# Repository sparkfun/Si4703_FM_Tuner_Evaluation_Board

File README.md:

SparkFun FM Tuner Evaluation Board - Si4703
===========================================

[*SparkFun FM Tuner Evaluation Board - Si4703 (WRL-12938)*](https://www.sparkfun.com/products/12938)

This is an evaluation board for the Silicon Laboratories Si4703 FM tuner chip. Beyond being a simple FM radio, the Si4703 
is also capable of detecting and processing both Radio Data Service (RDS) and Radio Broadcast Data Service (RBDS) information. 

Repository Contents
-------------------
* **/Firmware** - Example code 
* **/Hardware** - Eagle design files (.brd, .sch)
* **/Libraries** - Libraries for use with the Si4703 Evaluation Board
* **/Production** - Production panel files (.brd)

Documentation
--------------
* **[Library](https://github.com/sparkfun/SparkFun_Si4703_Arduino_Library)** - Arduino and Raspberry Pi libraries for the Si4703.
* **[Hookup Guide](https://learn.sparkfun.com/tutorials/si4703-fm-radio-receiver-hookup-guide)** - Basic hookup guide for the Si4703.
* **[SparkFun Fritzing repo](https://github.com/sparkfun/Fritzing_Parts)** - Fritzing diagrams for SparkFun products.
* **[SparkFun 3D Model repo](https://github.com/sparkfun/3D_Models)** - 3D models of SparkFun products. 

License Information
-------------------
This product is _**open source**_! 

Please review the LICENSE.md file for license information. 

If you have any questions or concerns on licensing, please contact techsupport@sparkfun.com.

Distributed as-is; no warranty is given.

- Your friends at SparkFun.

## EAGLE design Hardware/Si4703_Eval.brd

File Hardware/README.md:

SparkFun Si4703 Evaluation Board Design Files
============================================

The .sch and .brd files hare are Eagle CAD schematic and PCB design files from SparkFun Electronics.
A freeware version of Eagle can be found [here](http://www.cadsoftusa.com/download-eagle/freeware/). 

License
---------
This product is open source! 
The hardware is released under [Creative Commons ShareAlike 4.0 International](https://creativecommons.org/licenses/by-sa/4.0/).

Please use, reuse, and modify these files as you see fit. Please maintain attribution to SparkFun Electronics and release anything derivative under the same license.

Distributed as-is; no warranty is given.

- Your friends at SparkFun.

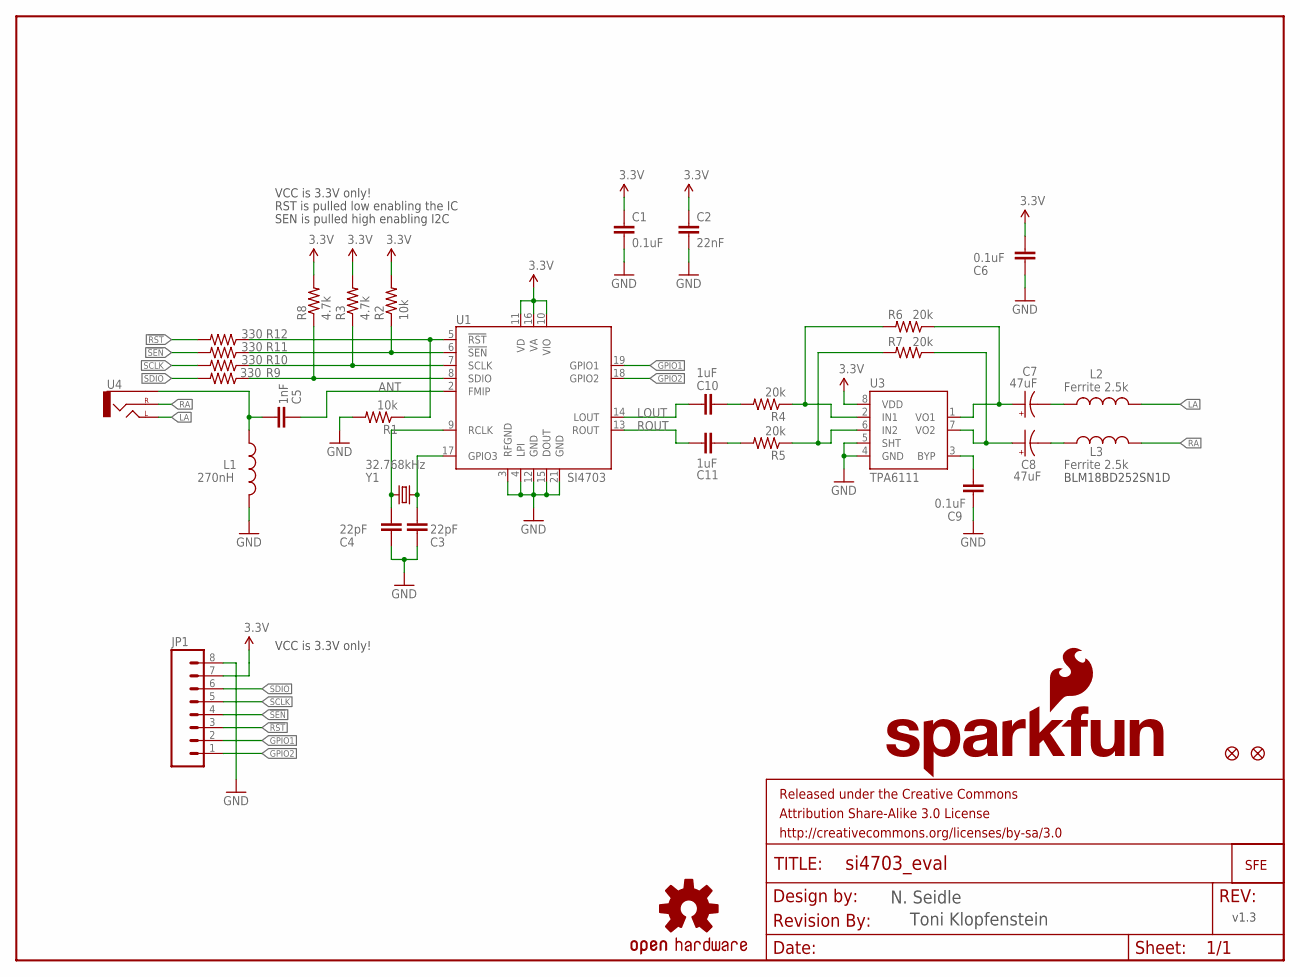
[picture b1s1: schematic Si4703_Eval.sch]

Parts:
C1, C6, C9: 0.1uF; 0603-CAP
C2: 22nF; 0603-CAP
C3, C4: 22pF; 0603-CAP
C5: 1nF; 0603-CAP
C7, C8: 47uF; EIA3528
C10, C11: 1uF; 0603-CAP
FRAME2: FRAME-LETTER; CREATIVE_COMMONS
JP1: M08; 1X08
JP3: LOGO-SFESK; SFE-LOGO-FLAME
JP4, JP5: FIDUCIAL1X2; FIDUCIAL-1X2
L1: 270nH; 0603
L2, L3: Ferrite 2.5k; 0603
LOGO1: SFE_LOGO_NAME_FLAME.1_INCH; SFE_LOGO_NAME_FLAME_.1
LOGO2: OSHW-LOGOS; OSHW-LOGO-S
R1, R2: 10k; 0603-RES
R3, R8: 4.7k; 0603
R4, R5, R6, R7: 20k; 0603-RES
R9, R10, R11, R12: 330; 0603-RES
U1: SI4703; SI470X
U3: TPA6111; SO08-TIGHT
U4: AUDIO-JACKSMD2; AUDIO-JACK-3.5MM-SMD
U$1: REVISION
Y1: 32.768kHz; CRYSTAL-32KHZ-SMD

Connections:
3.3V: C1.1, C2.1, C6.2, JP1.7, R2.2, R3.2, R8.2, U1.10 (VIO), U1.11 (VD), U1.16 (VA), U3.8 (VDD)
!RST: JP1.3, R12.2
!RST-L: R1.1, R12.1, U1.5 (!RST)
!SEN: JP1.4, R11.2
!SEN-L: R2.1, R11.1, U1.6 (!SEN)
ANT: C5.1, U1.2 (FMIP)
GND: C1.2, C2.2, C3.1, C4.1, C6.1, C9.2, JP1.8, L1.2, R1.2, U1.3 (RFGND), U1.4 (LPI), U1.12 (GND), U1.15 (DOUT), U1.21 (GND), U3.4 (GND), U3.5 (SHT)
GPIO1: JP1.2, U1.19 (GPIO1)
GPIO2: JP1.1, U1.18 (GPIO2)
LA: L2.2, U4.TIP (LEFT)
LOUT: C10.1, U1.14 (LOUT)
unnamed: C4.2, U1.9 (RCLK), Y1.X2 (2)
unnamed: C3.2, U1.17 (GPIO3), Y1.X1 (1)
unnamed: C5.2, L1.1, U4.SLEEVE
unnamed: C7.C (-), L2.1
unnamed: C7.A (+), R6.1, U3.1 (VO1)
unnamed: C8.A (+), R7.1, U3.7 (VO2)
unnamed: C8.C (-), L3.1
unnamed: C9.1, U3.3 (BYP)
unnamed: R4.1, R6.2, U3.2 (IN1)
unnamed: R5.1, R7.2, U3.6 (IN2)
unnamed: C10.2, R4.2
unnamed: C11.2, R5.2
RA: L3.2, U4.RING (RIGHT)
ROUT: C11.1, U1.13 (ROUT)
SCLK: JP1.5, R10.2
SCLK-L: R3.1, R10.1, U1.7 (SCLK)
SDIO: JP1.6, R9.2
SDIO-L: R8.1, R9.1, U1.8 (SDIO)

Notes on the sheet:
VCC is 3.3V only!
N. Seidle
BLM18BD252SN1D
SEN is pulled high enabling I2C
RST is pulled low enabling the IC
v1.3
Toni Klopfenstein

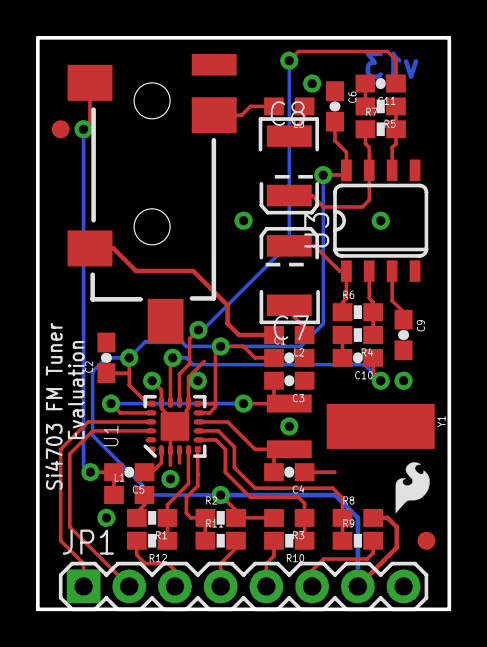
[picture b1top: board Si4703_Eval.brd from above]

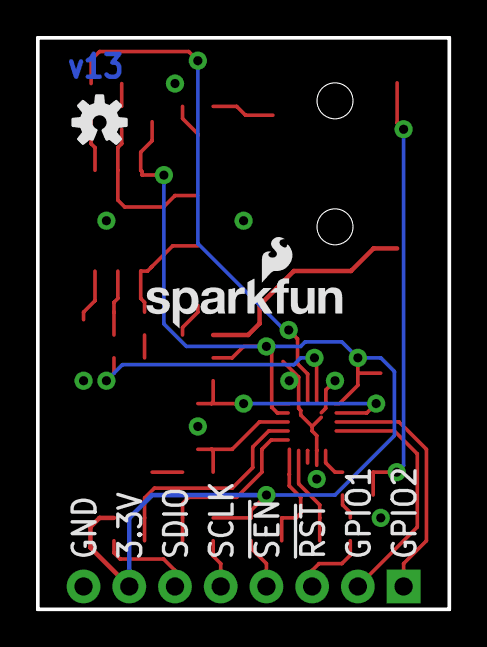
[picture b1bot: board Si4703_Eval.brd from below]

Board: 2 copper layers, 22.9 x 31.8 mm, 38 parts (2 on the bottom side), 29 nets.

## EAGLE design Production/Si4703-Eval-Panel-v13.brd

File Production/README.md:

SparkFun Si4703 Evaluation Board Production Files
==================================================

These are the production files SparkFun uses for printing PCBs.

License Information
-------------------
This product is open source! 

The hardware is released under [Creative Commons ShareAlike 4.0 International](https://creativecommons.org/licenses/by-sa/4.0/).

Please use, reuse, and modify these files as you see fit. Please maintain attribution to SparkFun Electronics and release anything derivative under the same license.

Distributed as-is; no warranty is given.

- Your friends at SparkFun.

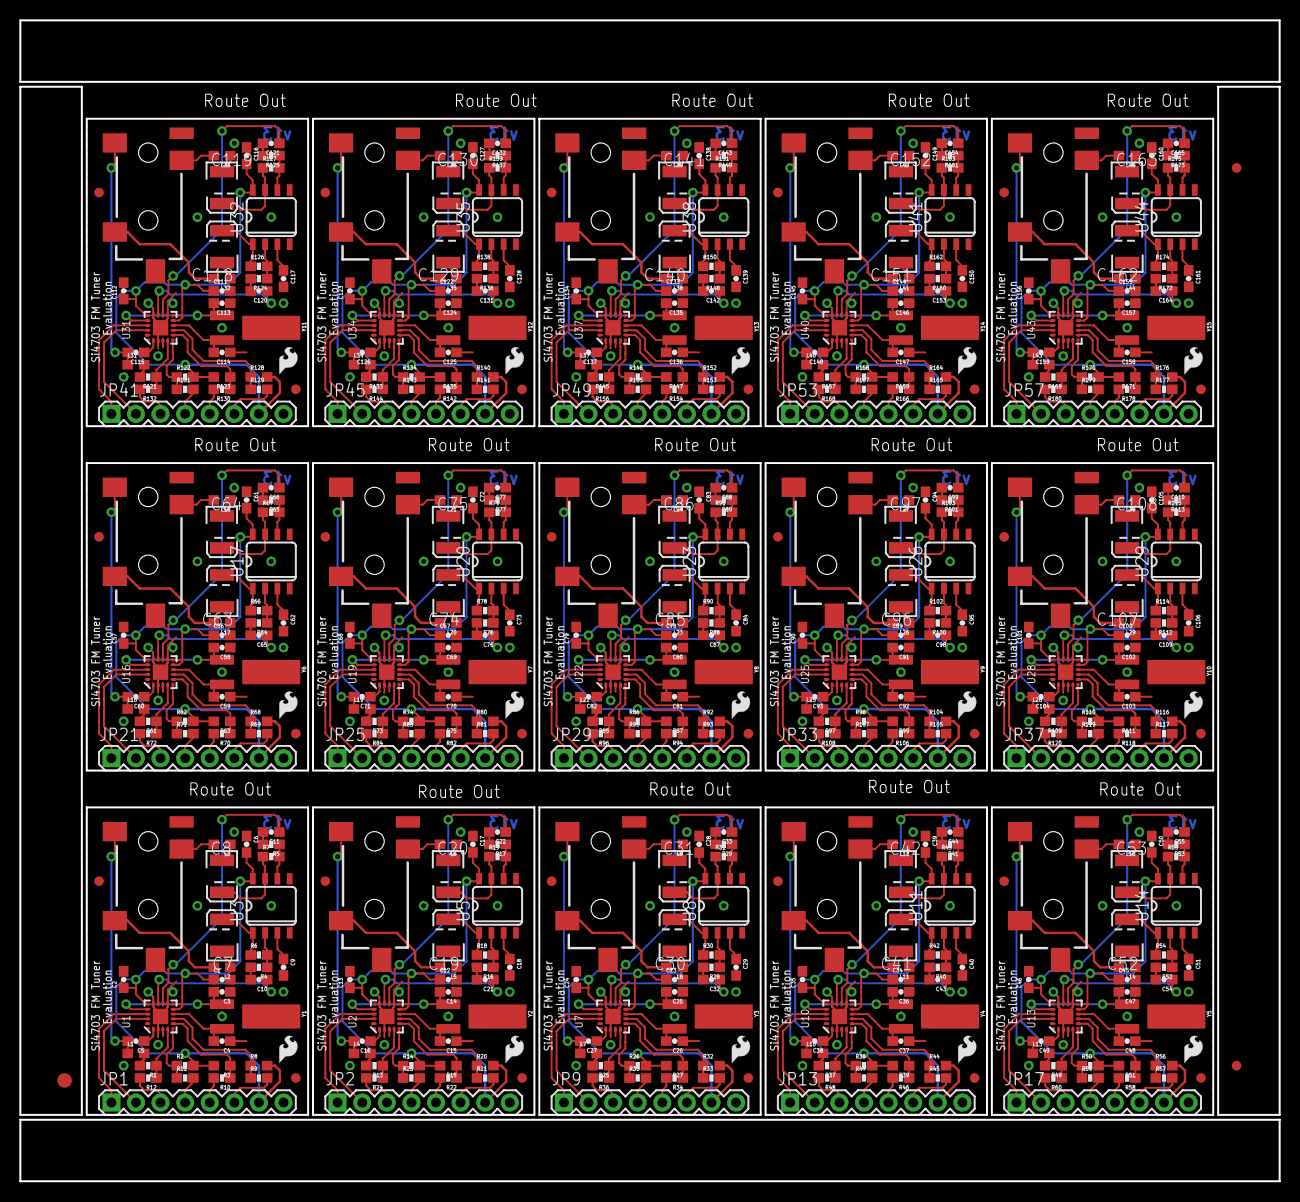
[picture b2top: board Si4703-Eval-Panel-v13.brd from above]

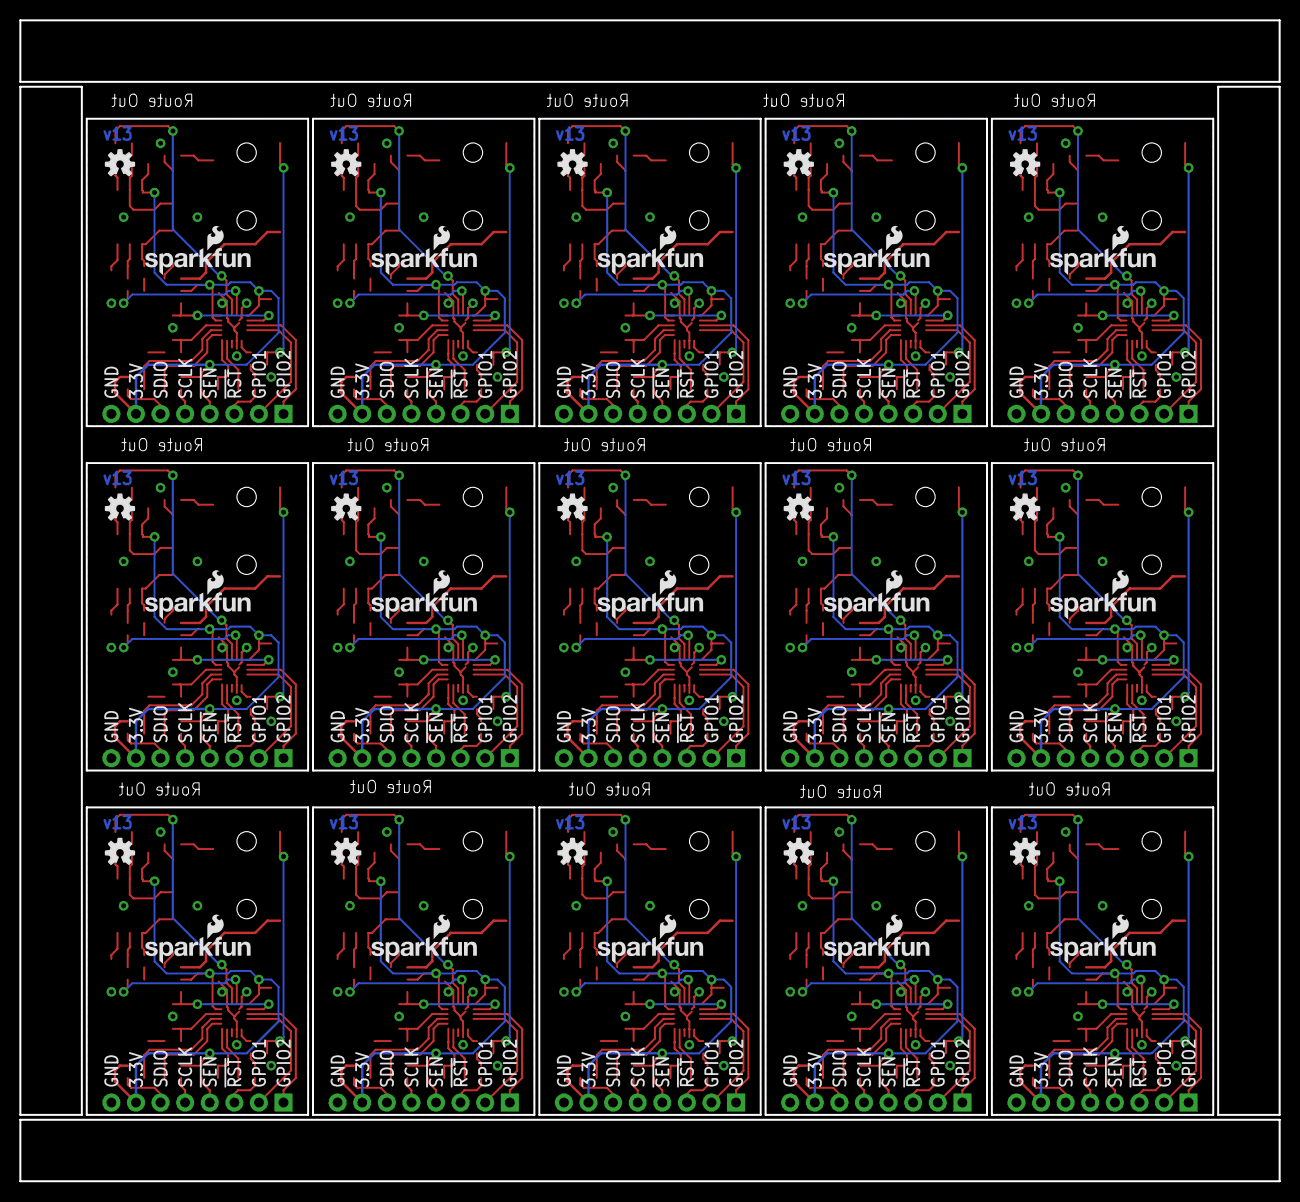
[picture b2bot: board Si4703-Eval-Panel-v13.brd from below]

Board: 2 copper layers, 130.0 x 119.9 mm, 543 parts (30 on the bottom side), 435 nets.

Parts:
C1, C6, C9, C12, C17, C18, C23, C28, C29, C34, C39, C40, C45, C50, C51, C56, C61, C62, C67, C72, C73, C78, C83, C84, C89, C94, C95, C100, C105, C106, C111, C116, C117, C122, C127, C128, C133, C138, C139, C144, C149, C150, C155, C160, C161: 0.1uF; 0603-CAP
C2, C13, C24, C35, C46, C57, C68, C79, C90, C101, C112, C123, C134, C145, C156: 22nF; 0603-CAP
C3, C4, C14, C15, C25, C26, C36, C37, C47, C48, C58, C59, C69, C70, C80, C81, C91, C92, C102, C103, C113, C114, C124, C125, C135, C136, C146, C147, C157, C158: 22pF; 0603-CAP
C5, C16, C27, C38, C49, C60, C71, C82, C93, C104, C115, C126, C137, C148, C159: 1nF; 0603-CAP
C7, C8, C19, C20, C30, C31, C41, C42, C52, C53, C63, C64, C74, C75, C85, C86, C96, C97, C107, C108, C118, C119, C129, C130, C140, C141, C151, C152, C162, C163: 47uF; EIA3528
C10, C11, C21, C22, C32, C33, C43, C44, C54, C55, C65, C66, C76, C77, C87, C88, C98, C99, C109, C110, C120, C121, C131, C132, C142, C143, C153, C154, C164, C165: 1uF; 0603-CAP
E$1: FIDUCIAL-1.5X3
E$4, E$5: FIDUCIAL-1X2
JP1, JP2, JP9, JP13, JP17, JP21, JP25, JP29, JP33, JP37, JP41, JP45, JP49, JP53, JP57: 1X08
JP3, JP6, JP10, JP14, JP18, JP22, JP26, JP30, JP34, JP38, JP42, JP46, JP50, JP54, JP58: LOGO-SFESK; SFE-LOGO-FLAME
JP4, JP5, JP7, JP8, JP11, JP12, JP15, JP16, JP19, JP20, JP23, JP24, JP27, JP28, JP31, JP32, JP35, JP36, JP39, JP40, JP43, JP44, JP47, JP48, JP51, JP52, JP55, JP56, JP59, JP60: FIDUCIAL1X2; FIDUCIAL-1X2
L1, L4, L7, L10, L13, L16, L19, L22, L25, L28, L31, L34, L37, L40, L43: 270nH; 0603
L2, L3, L5, L6, L8, L9, L11, L12, L14, L15, L17, L18, L20, L21, L23, L24, L26, L27, L29, L30, L32, L33, L35, L36, L38, L39, L41, L42, L44, L45: Ferrite 2.5k; 0603
LOGO1, LOGO3, LOGO5, LOGO7, LOGO9, LOGO11, LOGO13, LOGO15, LOGO17, LOGO19, LOGO21, LOGO23, LOGO25, LOGO27, LOGO29: SFE_LOGO_NAME_FLAME.1_INCH; SFE_LOGO_NAME_FLAME_.1
LOGO2, LOGO4, LOGO6, LOGO8, LOGO10, LOGO12, LOGO14, LOGO16, LOGO18, LOGO20, LOGO22, LOGO24, LOGO26, LOGO28, LOGO30: OSHW-LOGOS; OSHW-LOGO-S
R1, R2, R13, R14, R25, R26, R37, R38, R49, R50, R61, R62, R73, R74, R85, R86, R97, R98, R109, R110, R121, R122, R133, R134, R145, R146, R157, R158, R169, R170: 10k; 0603-RES
R3, R8, R15, R20, R27, R32, R39, R44, R51, R56, R63, R68, R75, R80, R87, R92, R99, R104, R111, R116, R123, R128, R135, R140, R147, R152, R159, R164, R171, R176: 4.7k; 0603
R4, R5, R6, R7, R16, R17, R18, R19, R28, R29, R30, R31, R40, R41, R42, R43, R52, R53, R54, R55, R64, R65, R66, R67, R76, R77, R78, R79, R88, R89, R90, R91, R100, R101, R102, R103, R112, R113, R114, R115, R124, R125, R126, R127, R136, R137, R138, R139, R148, R149, R150, R151, R160, R161, R162, R163, R172, R173, R174, R175: 20k; 0603-RES
R9, R10, R11, R12, R21, R22, R23, R24, R33, R34, R35, R36, R45, R46, R47, R48, R57, R58, R59, R60, R69, R70, R71, R72, R81, R82, R83, R84, R93, R94, R95, R96, R105, R106, R107, R108, R117, R118, R119, R120, R129, R130, R131, R132, R141, R142, R143, R144, R153, R154, R155, R156, R165, R166, R167, R168, R177, R178, R179, R180: 330; 0603-RES
U1, U2, U7, U10, U13, U16, U19, U22, U25, U28, U31, U34, U37, U40, U43: SI4703; SI470X
U3, U5, U8, U11, U14, U17, U20, U23, U26, U29, U32, U35, U38, U41, U44: TPA6111; SO08-TIGHT
U4, U6, U9, U12, U15, U18, U21, U24, U27, U30, U33, U36, U39, U42, U45: AUDIO-JACK-3.5MM-SMD
Y1, Y2, Y3, Y4, Y5, Y6, Y7, Y8, Y9, Y10, Y11, Y12, Y13, Y14, Y15: 32.768kHz; CRYSTAL-32KHZ-SMD

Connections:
3.3V: C1.1, C2.1, C6.2, JP1.7, R2.2, R3.2, R8.2, U1.10, U1.11, U1.16, U3.8
3.3V1: C12.1, C13.1, C17.2, JP2.7, R14.2, R15.2, R20.2, U2.10, U2.11, U2.16, U5.8
3.3V2: C23.1, C24.1, C28.2, JP9.7, R26.2, R27.2, R32.2, U7.10, U7.11, U7.16, U8.8
3.3V3: C34.1, C35.1, C39.2, JP13.7, R38.2, R39.2, R44.2, U10.10, U10.11, U10.16, U11.8
3.3V4: C45.1, C46.1, C50.2, JP17.7, R50.2, R51.2, R56.2, U13.10, U13.11, U13.16, U14.8
3.3V5: C56.1, C57.1, C61.2, JP21.7, R62.2, R63.2, R68.2, U16.10, U16.11, U16.16, U17.8
3.3V6: C67.1, C68.1, C72.2, JP25.7, R74.2, R75.2, R80.2, U19.10, U19.11, U19.16, U20.8
3.3V7: C78.1, C79.1, C83.2, JP29.7, R86.2, R87.2, R92.2, U22.10, U22.11, U22.16, U23.8
3.3V8: C89.1, C90.1, C94.2, JP33.7, R98.2, R99.2, R104.2, U25.10, U25.11, U25.16, U26.8
3.3V9: C100.1, C101.1, C105.2, JP37.7, R110.2, R111.2, R116.2, U28.10, U28.11, U28.16, U29.8
3.3V10: C111.1, C112.1, C116.2, JP41.7, R122.2, R123.2, R128.2, U31.10, U31.11, U31.16, U32.8
3.3V11: C122.1, C123.1, C127.2, JP45.7, R134.2, R135.2, R140.2, U34.10, U34.11, U34.16, U35.8
3.3V12: C133.1, C134.1, C138.2, JP49.7, R146.2, R147.2, R152.2, U37.10, U37.11, U37.16, U38.8
3.3V13: C144.1, C145.1, C149.2, JP53.7, R158.2, R159.2, R164.2, U40.10, U40.11, U40.16, U41.8
3.3V14: C155.1, C156.1, C160.2, JP57.7, R170.2, R171.2, R176.2, U43.10, U43.11, U43.16, U44.8
!RST: JP1.3, R12.2
!RST1: JP2.3, R24.2
!RST2: JP9.3, R36.2
!RST3: JP13.3, R48.2
!RST4: JP17.3, R60.2
!RST5: JP21.3, R72.2
!RST6: JP25.3, R84.2
!RST7: JP29.3, R96.2
!RST8: JP33.3, R108.2
!RST9: JP37.3, R120.2
!RST10: JP41.3, R132.2
!RST11: JP45.3, R144.2
!RST12: JP49.3, R156.2
!RST13: JP53.3, R168.2
!RST14: JP57.3, R180.2
!RST-L: R1.1, R12.1, U1.5
!RST-L1: R13.1, R24.1, U2.5
!RST-L2: R25.1, R36.1, U7.5
!RST-L3: R37.1, R48.1, U10.5
!RST-L4: R49.1, R60.1, U13.5
!RST-L5: R61.1, R72.1, U16.5
!RST-L6: R73.1, R84.1, U19.5
!RST-L7: R85.1, R96.1, U22.5
!RST-L8: R97.1, R108.1, U25.5
!RST-L9: R109.1, R120.1, U28.5
!RST-L10: R121.1, R132.1, U31.5
!RST-L11: R133.1, R144.1, U34.5
!RST-L12: R145.1, R156.1, U37.5
!RST-L13: R157.1, R168.1, U40.5
!RST-L14: R169.1, R180.1, U43.5
!SEN: JP1.4, R11.2
!SEN1: JP2.4, R23.2
!SEN2: JP9.4, R35.2
!SEN3: JP13.4, R47.2
!SEN4: JP17.4, R59.2
!SEN5: JP21.4, R71.2
!SEN6: JP25.4, R83.2
!SEN7: JP29.4, R95.2
!SEN8: JP33.4, R107.2
!SEN9: JP37.4, R119.2
!SEN10: JP41.4, R131.2
!SEN11: JP45.4, R143.2
!SEN12: JP49.4, R155.2
!SEN13: JP53.4, R167.2
!SEN14: JP57.4, R179.2
!SEN-L: R2.1, R11.1, U1.6
!SEN-L1: R14.1, R23.1, U2.6
!SEN-L2: R26.1, R35.1, U7.6
!SEN-L3: R38.1, R47.1, U10.6
!SEN-L4: R50.1, R59.1, U13.6
!SEN-L5: R62.1, R71.1, U16.6
!SEN-L6: R74.1, R83.1, U19.6
!SEN-L7: R86.1, R95.1, U22.6
!SEN-L8: R98.1, R107.1, U25.6
!SEN-L9: R110.1, R119.1, U28.6
!SEN-L10: R122.1, R131.1, U31.6
!SEN-L11: R134.1, R143.1, U34.6
!SEN-L12: R146.1, R155.1, U37.6
!SEN-L13: R158.1, R167.1, U40.6
!SEN-L14: R170.1, R179.1, U43.6
ANT: C5.1, U1.2
ANT1: C16.1, U2.2
ANT2: C27.1, U7.2
ANT3: C38.1, U10.2
ANT4: C49.1, U13.2
ANT5: C60.1, U16.2
ANT6: C71.1, U19.2
ANT7: C82.1, U22.2
ANT8: C93.1, U25.2
ANT9: C104.1, U28.2
ANT10: C115.1, U31.2
ANT11: C126.1, U34.2
ANT12: C137.1, U37.2
ANT13: C148.1, U40.2
ANT14: C159.1, U43.2
GND: C1.2, C2.2, C3.1, C4.1, C6.1, C9.2, JP1.8, L1.2, R1.2, U1.3, U1.4, U1.12, U1.15, U1.21, U3.4, U3.5
GND1: C12.2, C13.2, C14.1, C15.1, C17.1, C18.2, JP2.8, L4.2, R13.2, U2.3, U2.4, U2.12, U2.15, U2.21, U5.4, U5.5
GND2: C23.2, C24.2, C25.1, C26.1, C28.1, C29.2, JP9.8, L7.2, R25.2, U7.3, U7.4, U7.12, U7.15, U7.21, U8.4, U8.5
GND3: C34.2, C35.2, C36.1, C37.1, C39.1, C40.2, JP13.8, L10.2, R37.2, U10.3, U10.4, U10.12, U10.15, U10.21, U11.4, U11.5
GND4: C45.2, C46.2, C47.1, C48.1, C50.1, C51.2, JP17.8, L13.2, R49.2, U13.3, U13.4, U13.12, U13.15, U13.21, U14.4, U14.5
GND5: C56.2, C57.2, C58.1, C59.1, C61.1, C62.2, JP21.8, L16.2, R61.2, U16.3, U16.4, U16.12, U16.15, U16.21, U17.4, U17.5
GND6: C67.2, C68.2, C69.1, C70.1, C72.1, C73.2, JP25.8, L19.2, R73.2, U19.3, U19.4, U19.12, U19.15, U19.21, U20.4, U20.5
GND7: C78.2, C79.2, C80.1, C81.1, C83.1, C84.2, JP29.8, L22.2, R85.2, U22.3, U22.4, U22.12, U22.15, U22.21, U23.4, U23.5
GND8: C89.2, C90.2, C91.1, C92.1, C94.1, C95.2, JP33.8, L25.2, R97.2, U25.3, U25.4, U25.12, U25.15, U25.21, U26.4, U26.5
GND9: C100.2, C101.2, C102.1, C103.1, C105.1, C106.2, JP37.8, L28.2, R109.2, U28.3, U28.4, U28.12, U28.15, U28.21, U29.4, U29.5
GND10: C111.2, C112.2, C113.1, C114.1, C116.1, C117.2, JP41.8, L31.2, R121.2, U31.3, U31.4, U31.12, U31.15, U31.21, U32.4, U32.5
GND11: C122.2, C123.2, C124.1, C125.1, C127.1, C128.2, JP45.8, L34.2, R133.2, U34.3, U34.4, U34.12, U34.15, U34.21, U35.4, U35.5
GND12: C133.2, C134.2, C135.1, C136.1, C138.1, C139.2, JP49.8, L37.2, R145.2, U37.3, U37.4, U37.12, U37.15, U37.21, U38.4, U38.5
GND13: C144.2, C145.2, C146.1, C147.1, C149.1, C150.2, JP53.8, L40.2, R157.2, U40.3, U40.4, U40.12, U40.15, U40.21, U41.4, U41.5
GND14: C155.2, C156.2, C157.1, C158.1, C160.1, C161.2, JP57.8, L43.2, R169.2, U43.3, U43.4, U43.12, U43.15, U43.21, U44.4, U44.5
GPIO1: JP1.2, U1.19
GPIO2: JP1.1, U1.18
GPIO3: JP2.2, U2.19
GPIO4: JP2.1, U2.18
GPIO5: JP9.2, U7.19
GPIO6: JP9.1, U7.18
GPIO7: JP13.2, U10.19
GPIO8: JP13.1, U10.18
GPIO9: JP17.2, U13.19
GPIO10: JP17.1, U13.18
GPIO11: JP21.2, U16.19
GPIO12: JP21.1, U16.18
GPIO13: JP25.2, U19.19
GPIO14: JP25.1, U19.18
GPIO15: JP29.2, U22.19
GPIO16: JP29.1, U22.18
GPIO17: JP33.2, U25.19
GPIO18: JP33.1, U25.18
GPIO19: JP37.2, U28.19
GPIO20: JP37.1, U28.18
GPIO21: JP41.2, U31.19
GPIO22: JP41.1, U31.18
GPIO23: JP45.2, U34.19
GPIO24: JP45.1, U34.18
GPIO25: JP49.2, U37.19
GPIO26: JP49.1, U37.18
GPIO27: JP53.2, U40.19
GPIO28: JP53.1, U40.18
GPIO29: JP57.2, U43.19
GPIO30: JP57.1, U43.18
LA: L2.2, U4.TIP
LA1: L5.2, U6.TIP
LA2: L8.2, U9.TIP
LA3: L11.2, U12.TIP
LA4: L14.2, U15.TIP
LA5: L17.2, U18.TIP
LA6: L20.2, U21.TIP
LA7: L23.2, U24.TIP
LA8: L26.2, U27.TIP
LA9: L29.2, U30.TIP
LA10: L32.2, U33.TIP
LA11: L35.2, U36.TIP
LA12: L38.2, U39.TIP
LA13: L41.2, U42.TIP
LA14: L44.2, U45.TIP
LOUT: C10.1, U1.14
LOUT1: C21.1, U2.14
LOUT2: C32.1, U7.14
LOUT3: C43.1, U10.14
LOUT4: C54.1, U13.14
LOUT5: C65.1, U16.14
LOUT6: C76.1, U19.14
LOUT7: C87.1, U22.14
LOUT8: C98.1, U25.14
LOUT9: C109.1, U28.14
LOUT10: C120.1, U31.14
LOUT11: C131.1, U34.14
LOUT12: C142.1, U37.14
LOUT13: C153.1, U40.14
LOUT14: C164.1, U43.14
unnamed: C4.2, U1.9, Y1.X2
unnamed: C3.2, U1.17, Y1.X1
unnamed: C5.2, L1.1, U4.SLEEVE
unnamed: C7.C, L2.1
unnamed: C7.A, R6.1, U3.1
unnamed: C8.A, R7.1, U3.7
unnamed: C8.C, L3.1
unnamed: C9.1, U3.3
unnamed: C15.2, U2.9, Y2.X2
unnamed: C14.2, U2.17, Y2.X1
unnamed: R4.1, R6.2, U3.2
unnamed: R5.1, R7.2, U3.6
unnamed: C10.2, R4.2
unnamed: C11.2, R5.2
unnamed: C16.2, L4.1, U6.SLEEVE
unnamed: C19.A, R18.1, U5.1
unnamed: C20.A, R19.1, U5.7
unnamed: C18.1, U5.3
unnamed: R16.1, R18.2, U5.2
unnamed: R17.1, R19.2, U5.6
unnamed: C21.2, R16.2
unnamed: C22.2, R17.2
unnamed: C19.C, L5.1
unnamed: C20.C, L6.1
unnamed: C26.2, U7.9, Y3.X2
unnamed: C25.2, U7.17, Y3.X1
unnamed: C27.2, L7.1, U9.SLEEVE
unnamed: C30.A, R30.1, U8.1
unnamed: C31.A, R31.1, U8.7
unnamed: C29.1, U8.3
unnamed: R28.1, R30.2, U8.2
unnamed: R29.1, R31.2, U8.6
unnamed: C32.2, R28.2
unnamed: C33.2, R29.2
unnamed: C30.C, L8.1
unnamed: C31.C, L9.1
unnamed: C37.2, U10.9, Y4.X2
unnamed: C36.2, U10.17, Y4.X1
unnamed: C38.2, L10.1, U12.SLEEVE
unnamed: C41.A, R42.1, U11.1
unnamed: C42.A, R43.1, U11.7
unnamed: C40.1, U11.3
unnamed: R40.1, R42.2, U11.2
unnamed: R41.1, R43.2, U11.6
unnamed: C43.2, R40.2
unnamed: C44.2, R41.2
unnamed: C41.C, L11.1
unnamed: C42.C, L12.1
unnamed: C48.2, U13.9, Y5.X2
unnamed: C47.2, U13.17, Y5.X1
unnamed: C49.2, L13.1, U15.SLEEVE
unnamed: C52.A, R54.1, U14.1
unnamed: C53.A, R55.1, U14.7
unnamed: C51.1, U14.3
unnamed: R52.1, R54.2, U14.2
unnamed: R53.1, R55.2, U14.6
unnamed: C54.2, R52.2
unnamed: C55.2, R53.2
unnamed: C52.C, L14.1
unnamed: C53.C, L15.1
unnamed: C59.2, U16.9, Y6.X2
unnamed: C58.2, U16.17, Y6.X1
unnamed: C60.2, L16.1, U18.SLEEVE
unnamed: C63.A, R66.1, U17.1
unnamed: C64.A, R67.1, U17.7
unnamed: C62.1, U17.3
unnamed: R64.1, R66.2, U17.2
unnamed: R65.1, R67.2, U17.6
unnamed: C65.2, R64.2
unnamed: C66.2, R65.2
unnamed: C63.C, L17.1
unnamed: C64.C, L18.1
unnamed: C70.2, U19.9, Y7.X2
unnamed: C69.2, U19.17, Y7.X1
unnamed: C71.2, L19.1, U21.SLEEVE
unnamed: C74.A, R78.1, U20.1
unnamed: C75.A, R79.1, U20.7
unnamed: C73.1, U20.3
unnamed: R76.1, R78.2, U20.2
unnamed: R77.1, R79.2, U20.6
unnamed: C76.2, R76.2
unnamed: C77.2, R77.2
unnamed: C74.C, L20.1
unnamed: C75.C, L21.1
unnamed: C81.2, U22.9, Y8.X2
unnamed: C80.2, U22.17, Y8.X1
unnamed: C82.2, L22.1, U24.SLEEVE
unnamed: C85.A, R90.1, U23.1
unnamed: C86.A, R91.1, U23.7
unnamed: C84.1, U23.3
unnamed: R88.1, R90.2, U23.2
unnamed: R89.1, R91.2, U23.6
unnamed: C87.2, R88.2
unnamed: C88.2, R89.2
unnamed: C85.C, L23.1
unnamed: C86.C, L24.1
unnamed: C92.2, U25.9, Y9.X2
unnamed: C91.2, U25.17, Y9.X1
unnamed: C93.2, L25.1, U27.SLEEVE
unnamed: C96.A, R102.1, U26.1
unnamed: C97.A, R103.1, U26.7
unnamed: C95.1, U26.3
unnamed: R100.1, R102.2, U26.2
unnamed: R101.1, R103.2, U26.6
unnamed: C98.2, R100.2
unnamed: C99.2, R101.2
unnamed: C96.C, L26.1
unnamed: C97.C, L27.1
unnamed: C103.2, U28.9, Y10.X2
unnamed: C102.2, U28.17, Y10.X1
unnamed: C104.2, L28.1, U30.SLEEVE
unnamed: C107.A, R114.1, U29.1
unnamed: C108.A, R115.1, U29.7
unnamed: C106.1, U29.3
unnamed: R112.1, R114.2, U29.2
unnamed: R113.1, R115.2, U29.6
unnamed: C109.2, R112.2
unnamed: C110.2, R113.2
unnamed: C107.C, L29.1
unnamed: C108.C, L30.1
unnamed: C114.2, U31.9, Y11.X2
unnamed: C113.2, U31.17, Y11.X1
unnamed: C115.2, L31.1, U33.SLEEVE
unnamed: C118.A, R126.1, U32.1
unnamed: C119.A, R127.1, U32.7
unnamed: C117.1, U32.3
unnamed: R124.1, R126.2, U32.2
unnamed: R125.1, R127.2, U32.6
unnamed: C120.2, R124.2
unnamed: C121.2, R125.2
unnamed: C118.C, L32.1
unnamed: C119.C, L33.1
unnamed: C125.2, U34.9, Y12.X2
unnamed: C124.2, U34.17, Y12.X1
unnamed: C126.2, L34.1, U36.SLEEVE
unnamed: C129.A, R138.1, U35.1
unnamed: C130.A, R139.1, U35.7
unnamed: C128.1, U35.3
unnamed: R136.1, R138.2, U35.2
unnamed: R137.1, R139.2, U35.6
unnamed: C131.2, R136.2
unnamed: C132.2, R137.2
unnamed: C129.C, L35.1
unnamed: C130.C, L36.1
unnamed: C136.2, U37.9, Y13.X2
unnamed: C135.2, U37.17, Y13.X1
unnamed: C137.2, L37.1, U39.SLEEVE
unnamed: C140.A, R150.1, U38.1
unnamed: C141.A, R151.1, U38.7
unnamed: C139.1, U38.3
unnamed: R148.1, R150.2, U38.2
unnamed: R149.1, R151.2, U38.6
unnamed: C142.2, R148.2
unnamed: C143.2, R149.2
unnamed: C140.C, L38.1
unnamed: C141.C, L39.1
unnamed: C147.2, U40.9, Y14.X2
unnamed: C146.2, U40.17, Y14.X1
unnamed: C148.2, L40.1, U42.SLEEVE
unnamed: C151.A, R162.1, U41.1
unnamed: C152.A, R163.1, U41.7
unnamed: C150.1, U41.3
unnamed: R160.1, R162.2, U41.2
unnamed: R161.1, R163.2, U41.6
unnamed: C153.2, R160.2
unnamed: C154.2, R161.2
unnamed: C151.C, L41.1
unnamed: C152.C, L42.1
unnamed: C158.2, U43.9, Y15.X2
unnamed: C157.2, U43.17, Y15.X1
unnamed: C159.2, L43.1, U45.SLEEVE
unnamed: C162.A, R174.1, U44.1
unnamed: C163.A, R175.1, U44.7
unnamed: C161.1, U44.3
unnamed: R172.1, R174.2, U44.2
unnamed: R173.1, R175.2, U44.6
unnamed: C164.2, R172.2
unnamed: C165.2, R173.2
unnamed: C162.C, L44.1
unnamed: C163.C, L45.1
RA: L3.2, U4.RING
RA1: L6.2, U6.RING
RA2: L9.2, U9.RING
RA3: L12.2, U12.RING
RA4: L15.2, U15.RING
RA5: L18.2, U18.RING
RA6: L21.2, U21.RING
RA7: L24.2, U24.RING
RA8: L27.2, U27.RING
RA9: L30.2, U30.RING
RA10: L33.2, U33.RING
RA11: L36.2, U36.RING
RA12: L39.2, U39.RING
RA13: L42.2, U42.RING
RA14: L45.2, U45.RING
ROUT: C11.1, U1.13
ROUT1: C22.1, U2.13
ROUT2: C33.1, U7.13
ROUT3: C44.1, U10.13
ROUT4: C55.1, U13.13
ROUT5: C66.1, U16.13
ROUT6: C77.1, U19.13
ROUT7: C88.1, U22.13
ROUT8: C99.1, U25.13
ROUT9: C110.1, U28.13
ROUT10: C121.1, U31.13
ROUT11: C132.1, U34.13
ROUT12: C143.1, U37.13
ROUT13: C154.1, U40.13
ROUT14: C165.1, U43.13
SCLK: JP1.5, R10.2
SCLK1: JP2.5, R22.2
SCLK2: JP9.5, R34.2
SCLK3: JP13.5, R46.2
SCLK4: JP17.5, R58.2
SCLK5: JP21.5, R70.2
SCLK6: JP25.5, R82.2
SCLK7: JP29.5, R94.2
SCLK8: JP33.5, R106.2
SCLK9: JP37.5, R118.2
SCLK10: JP41.5, R130.2
SCLK11: JP45.5, R142.2
SCLK12: JP49.5, R154.2
SCLK13: JP53.5, R166.2
SCLK14: JP57.5, R178.2
SCLK-L: R3.1, R10.1, U1.7
SCLK-L1: R15.1, R22.1, U2.7
SCLK-L2: R27.1, R34.1, U7.7
SCLK-L3: R39.1, R46.1, U10.7
SCLK-L4: R51.1, R58.1, U13.7
SCLK-L5: R63.1, R70.1, U16.7
SCLK-L6: R75.1, R82.1, U19.7
SCLK-L7: R87.1, R94.1, U22.7
SCLK-L8: R99.1, R106.1, U25.7
SCLK-L9: R111.1, R118.1, U28.7
SCLK-L10: R123.1, R130.1, U31.7
SCLK-L11: R135.1, R142.1, U34.7
SCLK-L12: R147.1, R154.1, U37.7
SCLK-L13: R159.1, R166.1, U40.7
SCLK-L14: R171.1, R178.1, U43.7
SDIO: JP1.6, R9.2
SDIO1: JP2.6, R21.2
SDIO2: JP9.6, R33.2
SDIO3: JP13.6, R45.2
SDIO4: JP17.6, R57.2
SDIO5: JP21.6, R69.2
SDIO6: JP25.6, R81.2
SDIO7: JP29.6, R93.2
SDIO8: JP33.6, R105.2
SDIO9: JP37.6, R117.2
SDIO10: JP41.6, R129.2
SDIO11: JP45.6, R141.2
SDIO12: JP49.6, R153.2
SDIO13: JP53.6, R165.2
SDIO14: JP57.6, R177.2
SDIO-L: R8.1, R9.1, U1.8
SDIO-L1: R20.1, R21.1, U2.8
SDIO-L2: R32.1, R33.1, U7.8
SDIO-L3: R44.1, R45.1, U10.8
SDIO-L4: R56.1, R57.1, U13.8
SDIO-L5: R68.1, R69.1, U16.8
SDIO-L6: R80.1, R81.1, U19.8
SDIO-L7: R92.1, R93.1, U22.8
SDIO-L8: R104.1, R105.1, U25.8
SDIO-L9: R116.1, R117.1, U28.8
SDIO-L10: R128.1, R129.1, U31.8
SDIO-L11: R140.1, R141.1, U34.8
SDIO-L12: R152.1, R153.1, U37.8
SDIO-L13: R164.1, R165.1, U40.8
SDIO-L14: R176.1, R177.1, U43.8

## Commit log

2013-06-28 Initial file upload for v12
2013-08-16 Update Si4703_Breakout.h
    more RDS decoding functions
2013-08-16 Update Si4703_Breakout.cpp
    more RDS decoding functions
2013-12-13 Code comment changes
    Removed references to datasheets that we were looking for, that have now
    been located (AN240 and AN243).
2013-12-13 Hardware changes to 0603 footprints and OSHW logo.
2014-05-19 fixing I2C breakout order, adding board name to file
2014-05-19 Fixing labels for 3.3V and GND
2014-06-30 Fixing review complaints on version number and upside down ground on schematic
2014-07-01 created panel v13
2015-05-14 Updating repo structure, adding documentation links, fixing names
2015-05-14 Squashed 'Libraries/Arduino/' content from commit 9eac801
    git-subtree-dir: Libraries/Arduino
    git-subtree-split: 9eac801e8865f5b5235ab0d2657a47cae651a9bb
2015-05-14 Updating readme
2017-10-08 Added functions to print out RDS and station name data.
2017-11-11 Changed delay from 30ms to 40ms.
2018-02-22 Copy of the Arduino library source.
    This code is unchanged, and will not currently compile on the
    Raspberry Pi.
2018-02-22 Cherry picked the RPi port from the rpi-si4703 project.
    The [rpi-si4703](https://github.com/cthoma/rpi-si4703.git) project
    is a Raspberry Pi port of the Arduino library from this repository.
    This change is a manual cherry-picking of that projects source
    at the a7344f425c5d3a8c5d83fe6e2a2954fc208eba74 commit with minor
    changes to correct file names. The Raspberry Pi port was done by
    thoma.christoph@gmx.at.
2018-02-24 Added Makefile, update README's.
    Also added RPi references to README.md files.
2018-02-24 Added clang-format Makefile target.
2018-02-24 Renamed member variables and moved down in class declaration.
2018-02-24 Formatted source using clang-format (i.e. `make format`).
    Also some manual comment formatting like adding punctuation
    and other minor edits.
2018-02-24 Deleted unneeded boolean/byte typedef's.
    byte was unused and boolean is provided by the language.
2018-02-24 Deleted si4703_init and si4703_exit.
    Moved their implementation (unchanged) into powerOn and powerOff
    respectively.
2018-02-24 Moved constant bit-shifting into header file.
    Doing this simplifies the source with little impact on
    header file readability.
2018-02-24 Added big/little endian swap functions.
    Just to improve readability.
2018-02-24 Removed unnecessary parenthesis around return values.
2018-02-24 Added a Region with support for Europe and the US.
2018-02-24 Created a SeekDirection enumeration.
    Converted from integer constants to enum class.
2018-02-24 Misc. fixes to comments.
2018-02-24 Using correct I2C device file.
    This isn't really correct yet.
2018-02-24 Added MAX_POWERUP_TIME and CLOCK_SETTLE_DELAY constants.
    And converted while(1) to while(true).
2018-02-24 Switched to tuning radio using MHz expressed with a float.
    Previously used a human readable integer "channel", like 885,
    which corresponded to 88.5 MHz, but was converted to a different
    "register channel" used by the Si4703. This changes switches to
    an even more human readable "frequency" (i.e. 88.), and the name
    "channel" is no longer overridden - it always means the Si4703
    register channel format (which varies by region).
2018-02-24 Added support for the radio band.
    This is US/Europe, Japan Wide, Japan.
2018-02-24 Added ChannelSpacing enum.
2018-02-24 Changed register variable name: registers_ → shadow_reg_.
    shadow_reg is what is used in the AN230 Programmers Guide, and
    it more clearly communicates that these are a copy of the actual
    chip registers.
    Additionally minor comment/formatting tweaks.
2018-02-24 Improvements to README.md.
2018-02-24 Improved public function documentation.
2018-02-24 Improved printRegisters.
    printRegisters now decodes registers and prints more than just their
    numerical values. In doing so also switched to C++ iostream for
    output.
2018-02-25 Added Scan program.
    Also made status methods public methods.
2018-02-25 Created a Status enum.
2018-02-25 Combined seekUp/seekDown into a single seek method.
2018-02-25 Spawning thread to read RDS data.
    This change will automatically spawn a thread when the radio is
    powered on. A condition variable returned by rdsCV() can be used
    to receive a signal that new RDS data has been received. At any
    time calling getRDS() will copy the current RDS text to the
    supplied buffer.
    The RDS thread is automatically terminated when the radio is
2018-09-10 Optimization
    Removed unnecessary while loop.
2018-09-12 Removed SCT Polling
    Enabled SCT interrupt and removed polling to prevent noise on bus from causing errors while tuning. Updated example code to reflect these changes.
2020-09-09 Renamed `CHIPID` constant to avoid name conflict.
    When building for the ESP8266 board, there is a name conflict with `CHIPID`,
    defined in a platform header, causing a compile failure.
    ```
    /path/to/esp8266_peri.h:28:31: error: expected unqualified-id before 'volatile'
    #define ESP8266_DREG(addr) *((volatile uint32_t *)(0x3FF00000+(addr)))
    ^
2020-09-17 Correctly implemented the seek/tune interrupt handling.
    The prior implementation was never correctly checking the interrupt
    pin (`_stcIntPin`) when seeking or tuning to a new channel. It was
    only checking that the pin variable, which contains the GPIO pin
    number, was non-zero - never the actual state of the pin. This
    resulted in the the code immediately concluding that the seek/tune
    operation was complete, that is unless `_stcIntPin` was set to zero,

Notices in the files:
parts and their libraries:
SparkFun-Aesthetics: Licensing: CC v3.0 Share-Alike You are welcome to use this library for commercial purposes.
SparkFun-Aesthetics: Released under the Creative Commons Attribution Share-Alike 3.0 License
SparkFun-Aesthetics: http://creativecommons.org/licenses/by-sa/3.0
